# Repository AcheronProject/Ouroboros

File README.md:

# Acheron Ouroboros

See [this page](https://gondolindrim.github.io/AcheronDocs/ouroboros/intro.html) for the Ouroboros documentation (still building).

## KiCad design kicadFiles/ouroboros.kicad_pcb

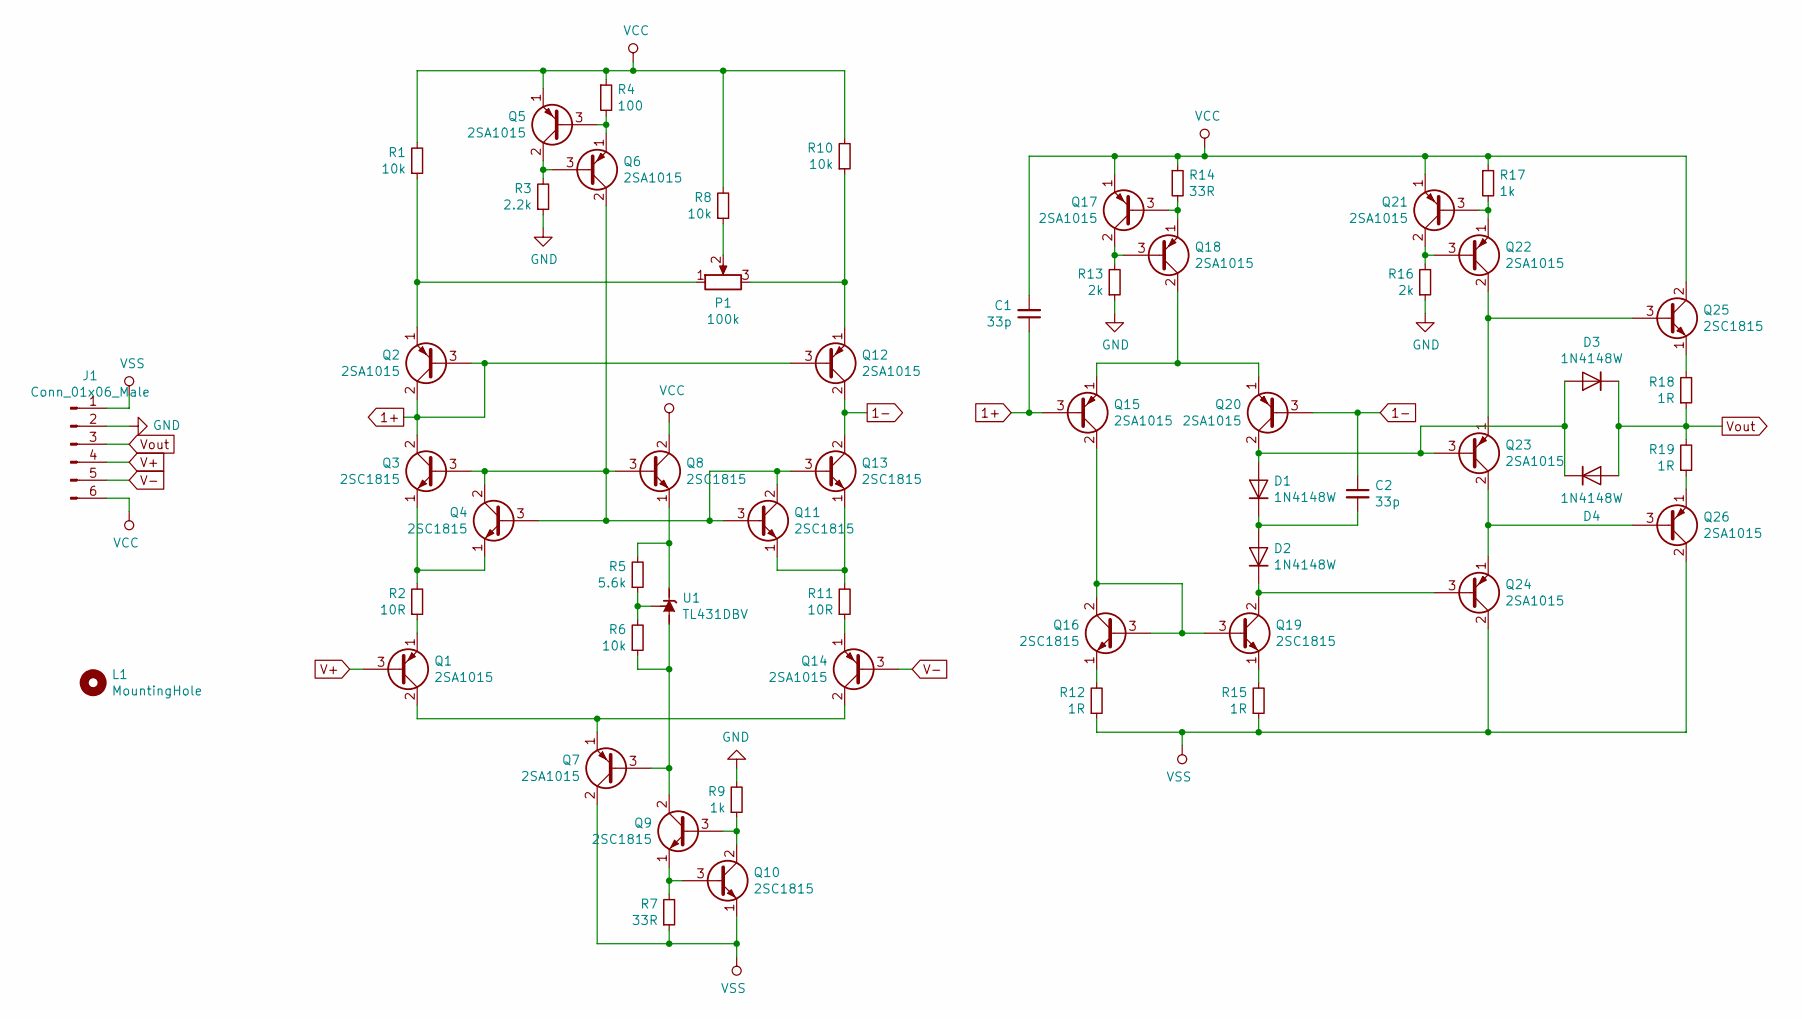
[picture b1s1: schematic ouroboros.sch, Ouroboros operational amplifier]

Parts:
C1, C2: 33p; C_0805_2012Metric_Pad1.15x1.40mm_HandSolder
D1, D2, D3, D4: 1N4148W; D_SOD-123
J1: Conn_01x06_Male; male6pinHeader
L1: MountingHole; ouroboros
P1: 100k; 3313J
Q1, Q2, Q5, Q6, Q7, Q12, Q14, Q15, Q17, Q18, Q20, Q21, Q22, Q23, Q24, Q26: 2SA1015; SOT-23
Q3, Q4, Q8, Q9, Q10, Q11, Q13, Q16, Q19, Q25: 2SC1815; SOT-23
R1, R6, R8, R10: 10k; R_0805_2012Metric_Pad1.15x1.40mm_HandSolder
R2, R11: 10R; R_0805_2012Metric_Pad1.15x1.40mm_HandSolder
R3: 2.2k; R_0805_2012Metric_Pad1.15x1.40mm_HandSolder
R4: 100; R_0805_2012Metric_Pad1.15x1.40mm_HandSolder
R5: 5.6k; R_0805_2012Metric_Pad1.15x1.40mm_HandSolder
R7, R14: 33R; R_0805_2012Metric_Pad1.15x1.40mm_HandSolder
R9, R17: 1k; R_0805_2012Metric_Pad1.15x1.40mm_HandSolder
R12, R15, R18, R19: 1R; R_0805_2012Metric_Pad1.15x1.40mm_HandSolder
R13, R16: 2k; R_0805_2012Metric_Pad1.15x1.40mm_HandSolder
U1: TL431DBV; SOT-23-5

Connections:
1+: C1.1, Q2.2 (C), Q2.3 (B), Q3.2 (C), Q12.3 (B), Q15.3 (B)
1-: C2.1, Q12.2 (C), Q13.2 (C), Q20.3 (B)
GND: J1.2, R3.1, R9.2, R13.1, R16.1
unnamed: C2.2, D1.1 (K), D2.2 (A)
unnamed: D1.2 (A), D3.2 (A), D4.1 (K), Q20.2 (C), Q23.3 (B)
unnamed: D2.1 (K), Q19.2 (C), Q24.3 (B)
unnamed: P1.1, Q2.1 (E), R1.1
unnamed: P1.2, R8.1
unnamed: P1.3, Q12.1 (E), R10.1
unnamed: Q1.1 (E), R2.1
unnamed: Q1.2 (C), Q7.1 (E), Q14.2 (C)
unnamed: Q3.1 (E), Q4.1 (E), R2.2
unnamed: Q5.2 (C), Q6.3 (B), R3.2
unnamed: Q5.3 (B), Q6.1 (E), R4.2
unnamed: Q7.3 (B), Q9.2 (C), R6.1, U1.5 (A)
unnamed: Q8.1 (E), R5.2, U1.3 (K)
unnamed: Q9.3 (B), Q10.2 (C), R9.1
unnamed: Q9.1 (E), Q10.3 (B), R7.2
unnamed: Q11.1 (E), Q13.1 (E), R11.2
unnamed: Q3.3 (B), Q4.2 (C), Q4.3 (B), Q6.2 (C), Q8.3 (B), Q11.2 (C), Q11.3 (B), Q13.3 (B)
unnamed: Q14.1 (E), R11.1
unnamed: Q15.1 (E), Q18.2 (C), Q20.1 (E)
unnamed: Q15.2 (C), Q16.2 (C), Q16.3 (B), Q19.3 (B)
unnamed: Q16.1 (E), R12.2
unnamed: Q17.2 (C), Q18.3 (B), R13.2
unnamed: Q17.3 (B), Q18.1 (E), R14.2
unnamed: Q19.1 (E), R15.2
unnamed: Q21.2 (C), Q22.3 (B), R16.2
unnamed: Q21.3 (B), Q22.1 (E), R17.2
unnamed: Q22.2 (C), Q23.1 (E), Q25.3 (B)
unnamed: Q23.2 (C), Q24.1 (E), Q26.3 (B)
unnamed: Q25.1 (E), R18.2
unnamed: Q26.1 (E), R19.1
unnamed: R5.1, R6.2, U1.4 (REF)
V+: J1.4, Q1.3 (B)
V-: J1.5, Q14.3 (B)
VCC: C1.2, J1.6, Q5.1 (E), Q8.2 (C), Q17.1 (E), Q21.1 (E), Q25.2 (C), R1.2, R4.1, R8.2, R10.2, R14.1, R17.1
VSS: J1.1, Q7.2 (C), Q10.1 (E), Q24.2 (C), Q26.2 (C), R7.1, R12.1, R15.1
Vout: D3.1 (K), D4.2 (A), J1.3, R18.1, R19.2

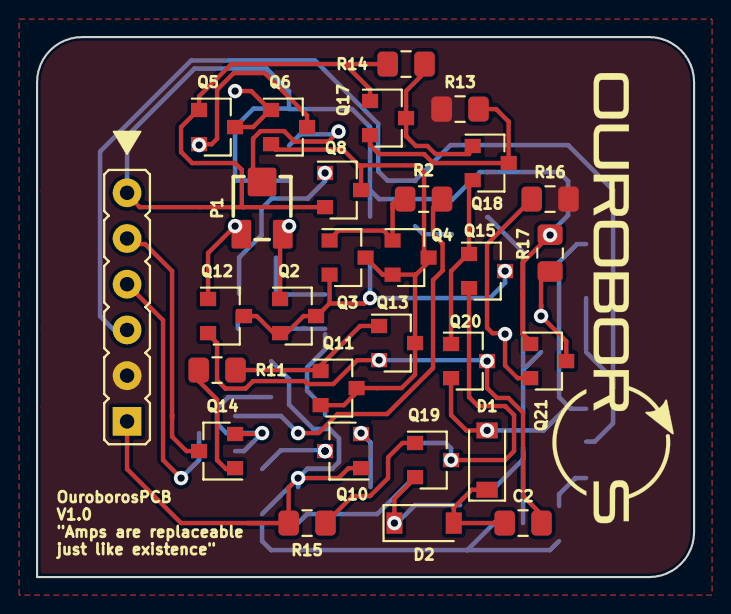
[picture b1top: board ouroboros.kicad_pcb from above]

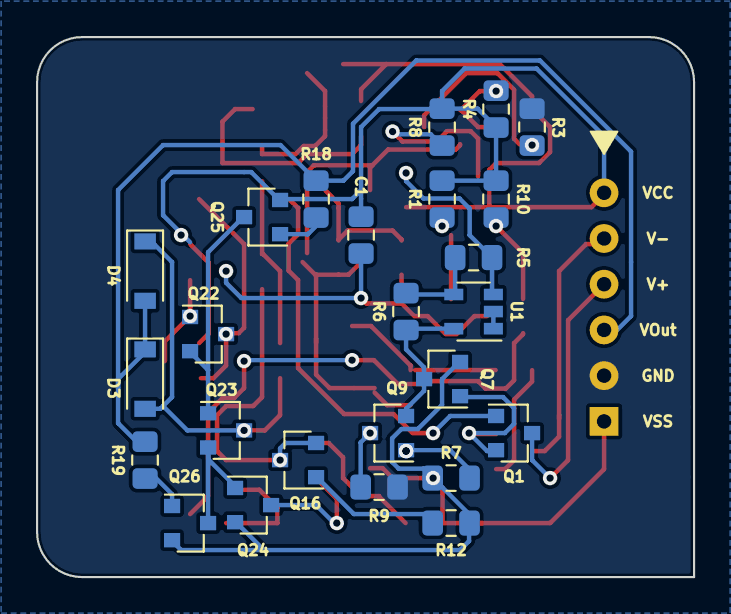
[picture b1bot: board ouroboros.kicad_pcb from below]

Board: 2 copper layers, 36.5 x 30.0 mm, 55 parts (25 on the bottom side), 39 nets.

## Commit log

2019-06-01 [Feature] Added README and LICENSE
2019-06-02 [Feature] Added CMRR, OL Gain, operating point and Slew Rate simulations
2019-06-06 Version 1.2 and 1.3 ideas
